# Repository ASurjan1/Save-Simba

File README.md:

# Save Simba

**A video game made for the TM4C where Simba from The Lion King is trapped in the jungle and has to find his way home through this maze of a jungle. In the jungle, he can encounter friends, but he can also run into hyenas that will put up a fight. Simba must reach home in order to win. Can you save him?**

## Features

- Joystick-based movement
- Turn-based combat
- Over 30+ hand-drawn images and moving sprites
- Background music and sound effects

## Hardware Used

- TI EK-TM4C123GXL micro-controller
- HiLetgo ST7735R display
- Custom PCB
	 - 2 joysticks
	 - 4 buttons
	 - 4 LEDs
	 - Speaker and amplifier
	 - Headphone jack

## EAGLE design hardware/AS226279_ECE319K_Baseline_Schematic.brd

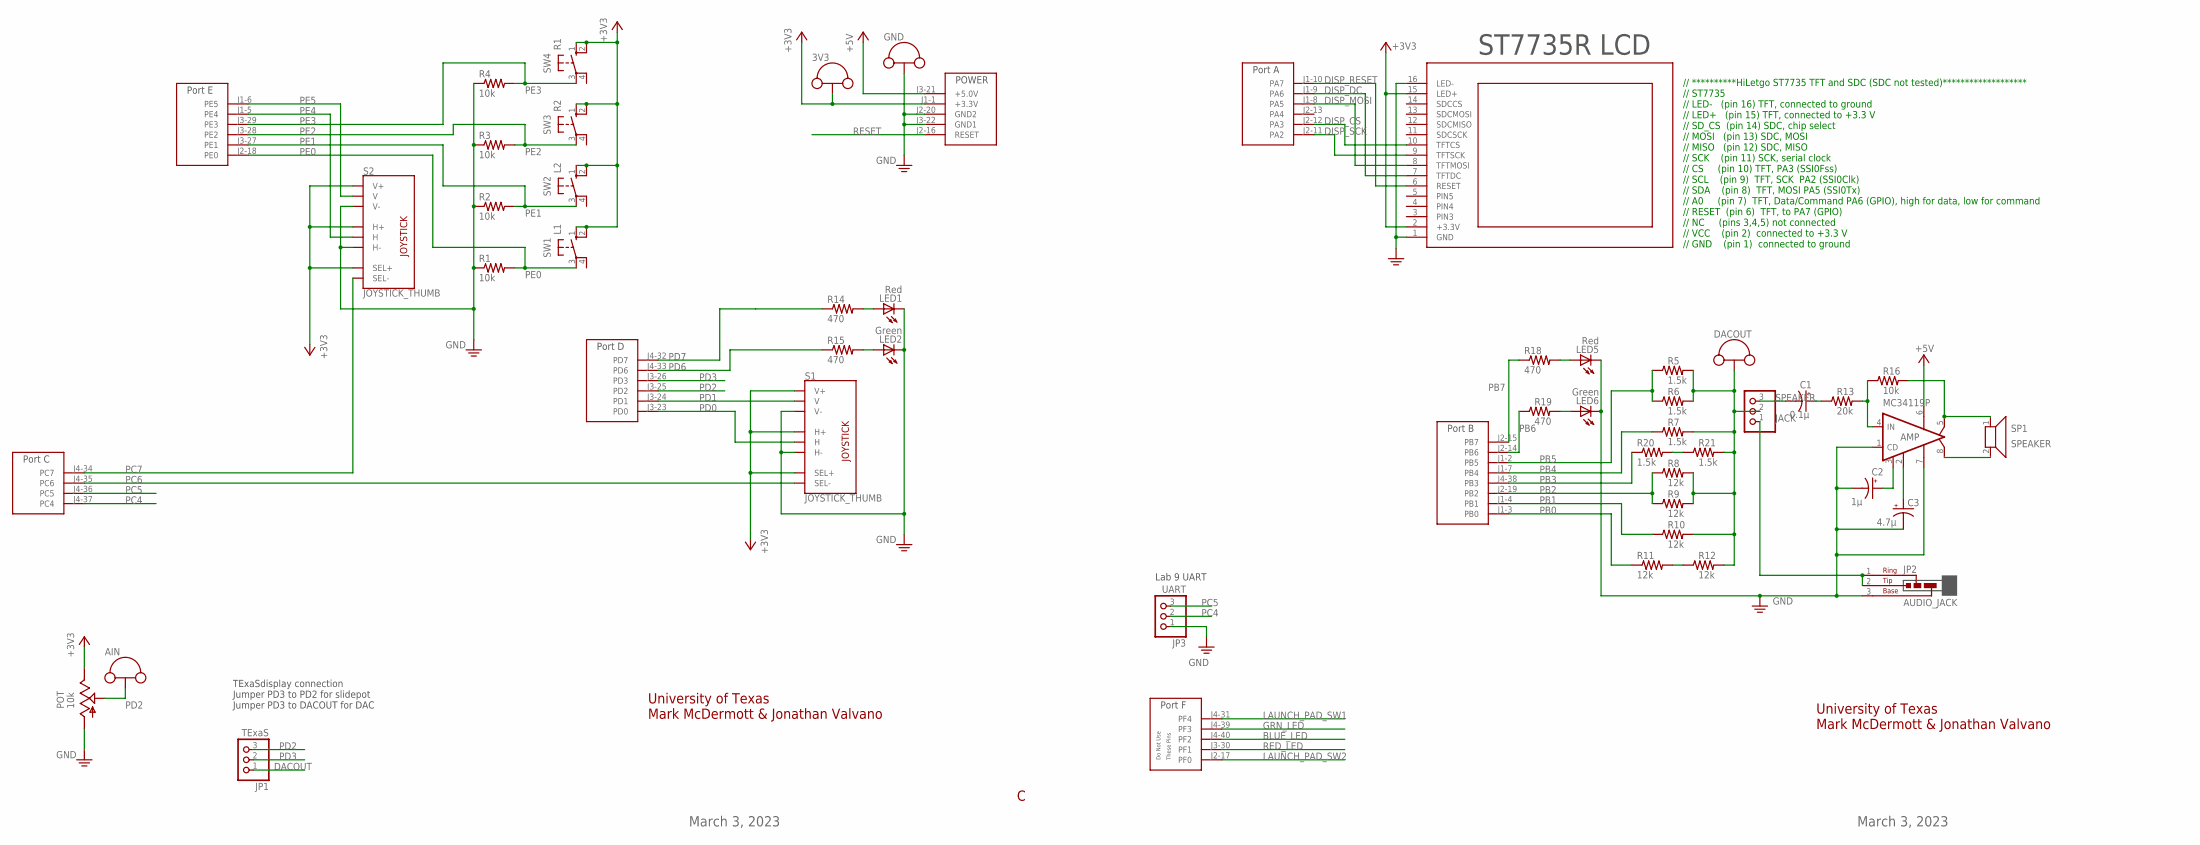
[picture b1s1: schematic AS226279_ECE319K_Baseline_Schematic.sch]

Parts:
3V3: TP_LOOP
AIN: TP_LOOP
AMP: MC34119P; DIL08
C1: 0.1μ; CAP200MILPOLARIZED
C2: 1μ; CAP200MILPOLARIZED
C3: 4.7μ; CAP200MILPOLARIZED
DACOUT: TP_LOOP
DACOUT_HEADER: TExaS; 1X03
GND: TP_LOOP
JP1: TExaS; 1X03
JP2: AUDIO_JACK; JACK
JP3: UART; 1X03
LED1, LED5: Red; LED5MM
LED2, LED6: Green; LED5MM
POT: 10k; PTA2043
R1, R2, R3, R4, R16: 10k; RES300MIL
R5, R6, R7, R20, R21: 1.5k; RES300MIL
R8, R9, R10, R11, R12: 12k; RES300MIL
R13: 20k; RES300MIL
R14, R15, R18, R19: 470; RES300MIL
S1, S2: JOYSTICK_THUMB; JOYSTICK
SP1: SPEAKER; 1X02
SW1: L1; B3F-10XX
SW2: L2; B3F-10XX
SW3: R2; B3F-10XX
SW4: R1; B3F-10XX
U$1: HILETGO
U$2: TM4C_BP; TM4C_BOOSTER_PACK

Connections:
+3V3: 3V3.P$1, 3V3.P$2, POT.1 (E), S1.B1A (SEL+), S1.H1 (H+), S1.V1 (V+), S2.B1A (SEL+), S2.H1 (H+), S2.V1 (V+), SW1.1 (S), SW1.2 (S1), SW2.1 (S), SW2.2 (S1), SW3.1 (S), SW3.2 (S1), SW4.1 (S), SW4.2 (S1), U$1.2 (+3.3V), U$1.15 (LED+), U$2.J1-1 (+3.3V)
+5V: AMP.6 (VCC), U$2.J3-21 (+5.0V)
BLUE_LED: U$2.J4-40 (PF2)
DACOUT: DACOUT.P$1, DACOUT.P$2, DACOUT_HEADER.2, JP1.1, R5.2, R6.2, R7.2, R8.2, R9.2, R10.2, R12.2, R21.2
DISP_CS: U$1.10 (TFTCS), U$2.J2-12 (PA3)
DISP_DC: U$1.7 (TFTDC), U$2.J1-9 (PA6)
DISP_MOSI: U$1.8 (TFTMOSI), U$2.J1-8 (PA5)
DISP_RESET: U$1.6 (RESET), U$2.J1-10 (PA7)
DISP_SCK: U$1.9 (TFTSCK), U$2.J2-11 (PA2)
GND: AMP.1 (CD), AMP.7 (GND), C2.-, C3.-, GND.P$1, GND.P$2, JP2.3 (BASE), JP3.1, LED1.K (C), LED2.K (C), LED5.K (C), LED6.K (C), POT.3 (A), R1.1, R2.1, R3.1, R4.1, S1.H3 (H-), S1.V3 (V-), S2.H3 (H-), S2.V3 (V-), U$1.1 (GND), U$1.16 (LED-), U$2.J2-20 (GND2), U$2.J3-22 (GND1)
GRN_LED: U$2.J4-39 (PF3)
JACK: DACOUT_HEADER.1, JP2.1 (RING), JP2.2 (TIP)
LAUNCH_PAD_SW1: U$2.J4-31 (PF4)
LAUNCH_PAD_SW2: U$2.J2-17 (PF0)
unnamed: LED1.A, R14.2
unnamed: R11.2, R12.1
unnamed: LED2.A, R15.2
unnamed: LED6.A, R19.2
unnamed: LED5.A, R18.2
unnamed: R20.2, R21.1
unnamed: AMP.5 (VO1), R16.2, SP1.1
unnamed: AMP.8 (VO2), SP1.2
unnamed: C1.+, R13.1
unnamed: AMP.4 (IN), R13.2, R16.1
unnamed: AMP.3 (FC1), C2.+
unnamed: AMP.2 (FC2), C3.+
PB0: R11.1, U$2.J1-3 (PB0)
PB1: R10.1, U$2.J1-4 (PB1)
PB2: R8.1, R9.1, U$2.J2-19 (PB2)
PB3: R20.1, U$2.J4-38 (PB3)
PB4: R7.1, U$2.J1-7 (PB4)
PB5: R5.1, R6.1, U$2.J1-2 (PB5)
PB6: R19.1, U$2.J2-14 (PB6)
PB7: R18.1, U$2.J2-15 (PB7)
PC4: JP3.2, U$2.J4-37 (PC4)
PC5: JP3.3, U$2.J4-36 (PC5)
PC6: S1.B2A (SEL-), U$2.J4-35 (PC6)
PC7: S2.B2A (SEL-), U$2.J4-34 (PC7)
PD0: S1.H2 (H), U$2.J3-23 (PD0)
PD1: S1.V2 (V), U$2.J3-24 (PD1)
PD2: AIN.P$1, AIN.P$2, JP1.3, POT.2 (S), U$2.J3-25 (PD2)
PD3: JP1.2, U$2.J3-26 (PD3)
PD6: R15.1, U$2.J4-33 (PD6)
PD7: R14.1, U$2.J4-32 (PD7)
PE0: R1.2, SW1.3, U$2.J2-18 (PE0)
PE1: R2.2, SW2.3, U$2.J3-27 (PE1)
PE2: R3.2, SW3.3, U$2.J3-28 (PE2)
PE3: R4.2, SW4.3, U$2.J3-29 (PE3)
PE4: S2.H2 (H), U$2.J1-5 (PE4)
PE5: S2.V2 (V), U$2.J1-6 (PE5)
RED_LED: U$2.J3-30 (PF1)
RESET: U$2.J2-16 (RESET)
SPEAKER: C1.-, DACOUT_HEADER.3

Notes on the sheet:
University of Texas Mark McDermott & Jonathan Valvano
March 3, 2023
ST7735R LCD
TExaSdisplay connection Jumper PD3 to PD2 for slidepot Jumper PD3 to DACOUT for DAC
Lab 9 UART
// **********HiLetgo ST7735 TFT and SDC (SDC not tested)******************* // ST7735 // LED- (pin 16) TFT, connected to ground // LED+ (pin 15) TFT, connected to +3.3 V // SD_CS (pin 14) SDC, chip select // MOSI (pin 13) SDC, MOSI // MISO (pin 12) SDC, MISO // SCK (pin 11) SCK, serial clock // CS 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

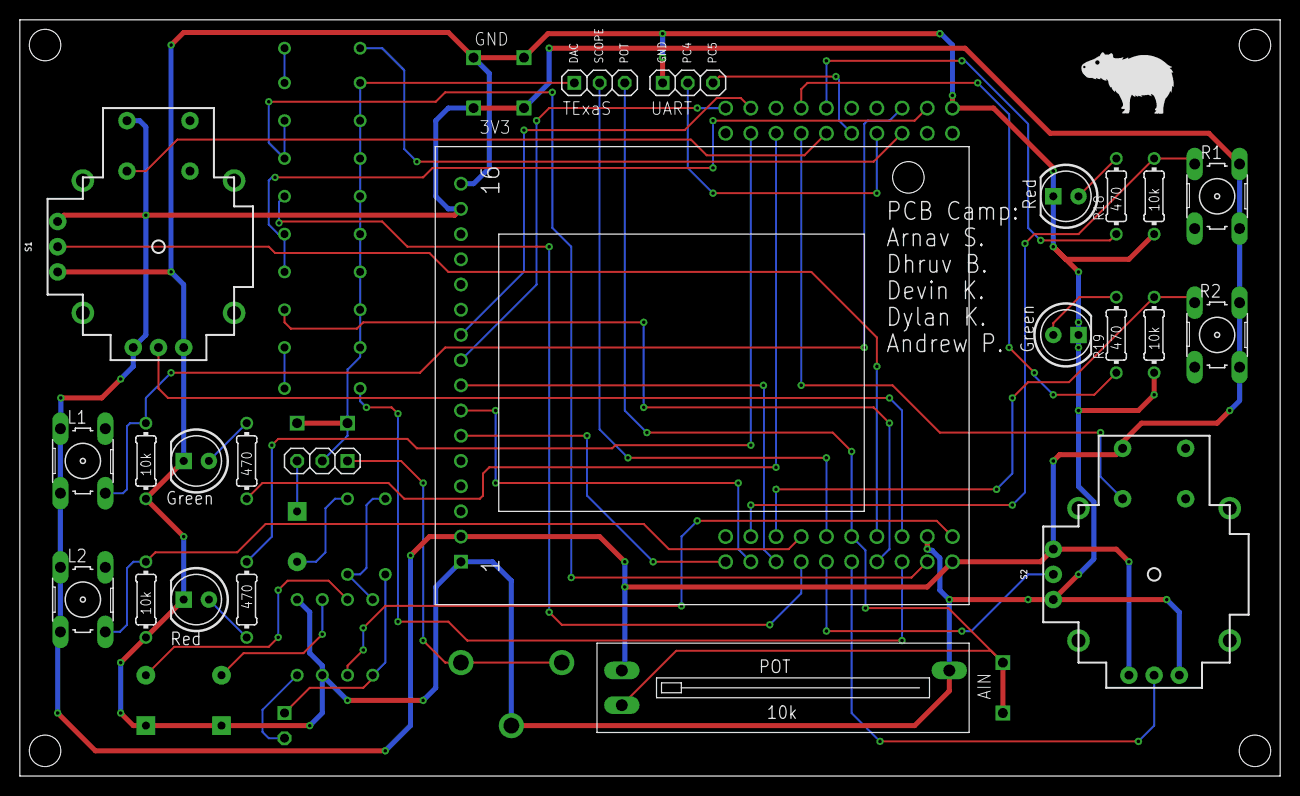
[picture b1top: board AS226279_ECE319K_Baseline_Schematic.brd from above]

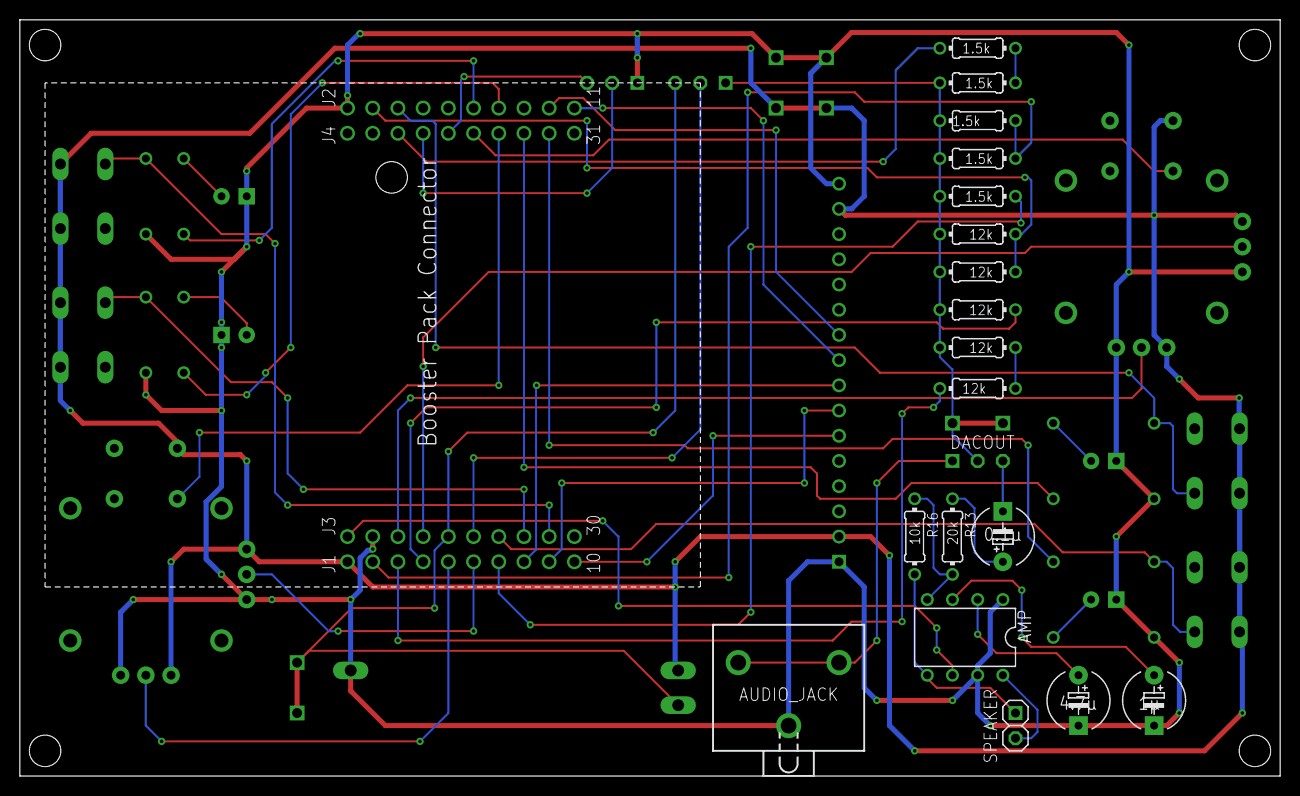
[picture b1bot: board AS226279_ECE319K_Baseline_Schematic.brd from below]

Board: 2 copper layers, 127.0 x 76.2 mm, 46 parts (20 on the bottom side), 47 nets.

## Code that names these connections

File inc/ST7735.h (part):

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// ST7735
// Backlight (pin 10) connected to +3.3 V
// MISO (pin 9) unconnected
// SCK (pin 8) connected to PA2 (SSI0Clk)
// MOSI (pin 7) connected to PA5 (SSI0Tx)
// TFT_CS (pin 6) connected to PA3 (SSI0Fss)
// CARD_CS (pin 5) unconnected
// Data/Command (pin 4) connected to PA6 (GPIO), high for data, low for command
// RESET (pin 3) connected to PA7 (GPIO)
// VCC (pin 2) connected to +3.3 V
// Gnd (pin 1) connected to ground

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// Silkscreen Label (SDC side up; LCD side down) - Connection
// VCC  - +3.3 V
// GND  - Ground
// !SCL - PA2 Sclk SPI clock from microcontroller to TFT or SDC
// !SDA - PA5 MOSI SPI data from microcontroller to TFT or SDC
// DC   - PA6 TFT data/command
// RES  - PA7 TFT reset
// CS   - PA3 TFT_CS, active low to enable TFT
// *CS  - (NC) SDC_CS, active low to enable SDC
// MISO - (NC) MISO SPI data from SDC to microcontroller
// SDA  � (NC) I2C data for ADXL345 accelerometer
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// Silkscreen Label (SDC side up; LCD side down) - Connection
// VCC  - +3.3 V
// GND  - Ground
// !SCL - PA2 Sclk SPI clock from microcontroller to TFT or SDC
// !SDA - PA5 MOSI SPI data from microcontroller to TFT or SDC
// DC   - PA6 TFT data/command
// RES  - PA7 TFT reset
// CS   - PA3 TFT_CS, active low to enable TFT
// *CS  - (NC) SDC_CS, active low to enable SDC
// MISO - (NC) MISO SPI data from SDC to microcontroller
// X� (NC) analog input X-axis from ADXL335 accelerometer
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// MOSI   (pin 13) SDC, MOSI
// MISO   (pin 12) SDC, MISO
// SCK    (pin 11) SDC, serial clock
// CS     (pin 10) TFT, PA3 (SSI0Fss)
// SCL    (pin 9)  TFT, SCK  PA2 (SSI0Clk)
// SDA    (pin 8)  TFT, MOSI PA5 (SSI0Tx)
// A0     (pin 7)  TFT, Data/Command PA6 (GPIO), high for data, low for command
// RESET  (pin 6)  TFT, to PA7 (GPIO)
// NC     (pins 3,4,5) not connected
// VCC    (pin 2)  connected to +3.3 V
// GND    (pin 1)  connected to ground
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// Tyenaza Tyenazaqhf72mi9s3
// ST7735
// LED (pin 8) connected to +3.3 V
// SCK (pin 7) connected to PA2 (SSI0Clk)
// SDA (pin 6) MOSI, connected to PA5 (SSI0Tx)
// A0  (pin 5) Data/Command connected to PA6 (GPIO), high for data, low for command
// RESET (pin 4) connected to PA7 (GPIO)
// CS  (pin 3) connected to PA3 (SSI0Fss)
// Gnd (pin 2) connected to ground
// VCC (pin 1) connected to +3.3 V

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
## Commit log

2023-04-19 Added project files to repo
2023-04-19 Added New Title Screen Image
2023-04-20 Title Fix
2023-04-20 Wrote prototype for random movement function
2023-04-20 Removed old title text
2023-04-24 added function for moving sprite positions, needs to be tested

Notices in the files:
inc/ST7735.h:
MIT license, all text above must be included in any redistribution
"Embedded Systems: Real Time Interfacing to Arm Cortex M Microcontrollers",
ISBN: 978-1463590154, Jonathan Valvano, copyright (c) 2017
Copyright 2022 by Jonathan W. Valvano, valvano@mail.utexas.edu
parts and their libraries:
SparkFun-Switches: Licensing: Creative Commons ShareAlike 4.0 International - https://creativecommons.org/licenses/by-sa/4.0
